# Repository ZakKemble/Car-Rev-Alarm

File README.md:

Car Rev Alarm and Gear Indicator
================================

A DIY Car rev alarm and gear indicator.

http://blog.zakkemble.co.uk/car-rev-alarm-and-gear-indicator/

---

Zak Kemble

contact@zakkemble.co.uk

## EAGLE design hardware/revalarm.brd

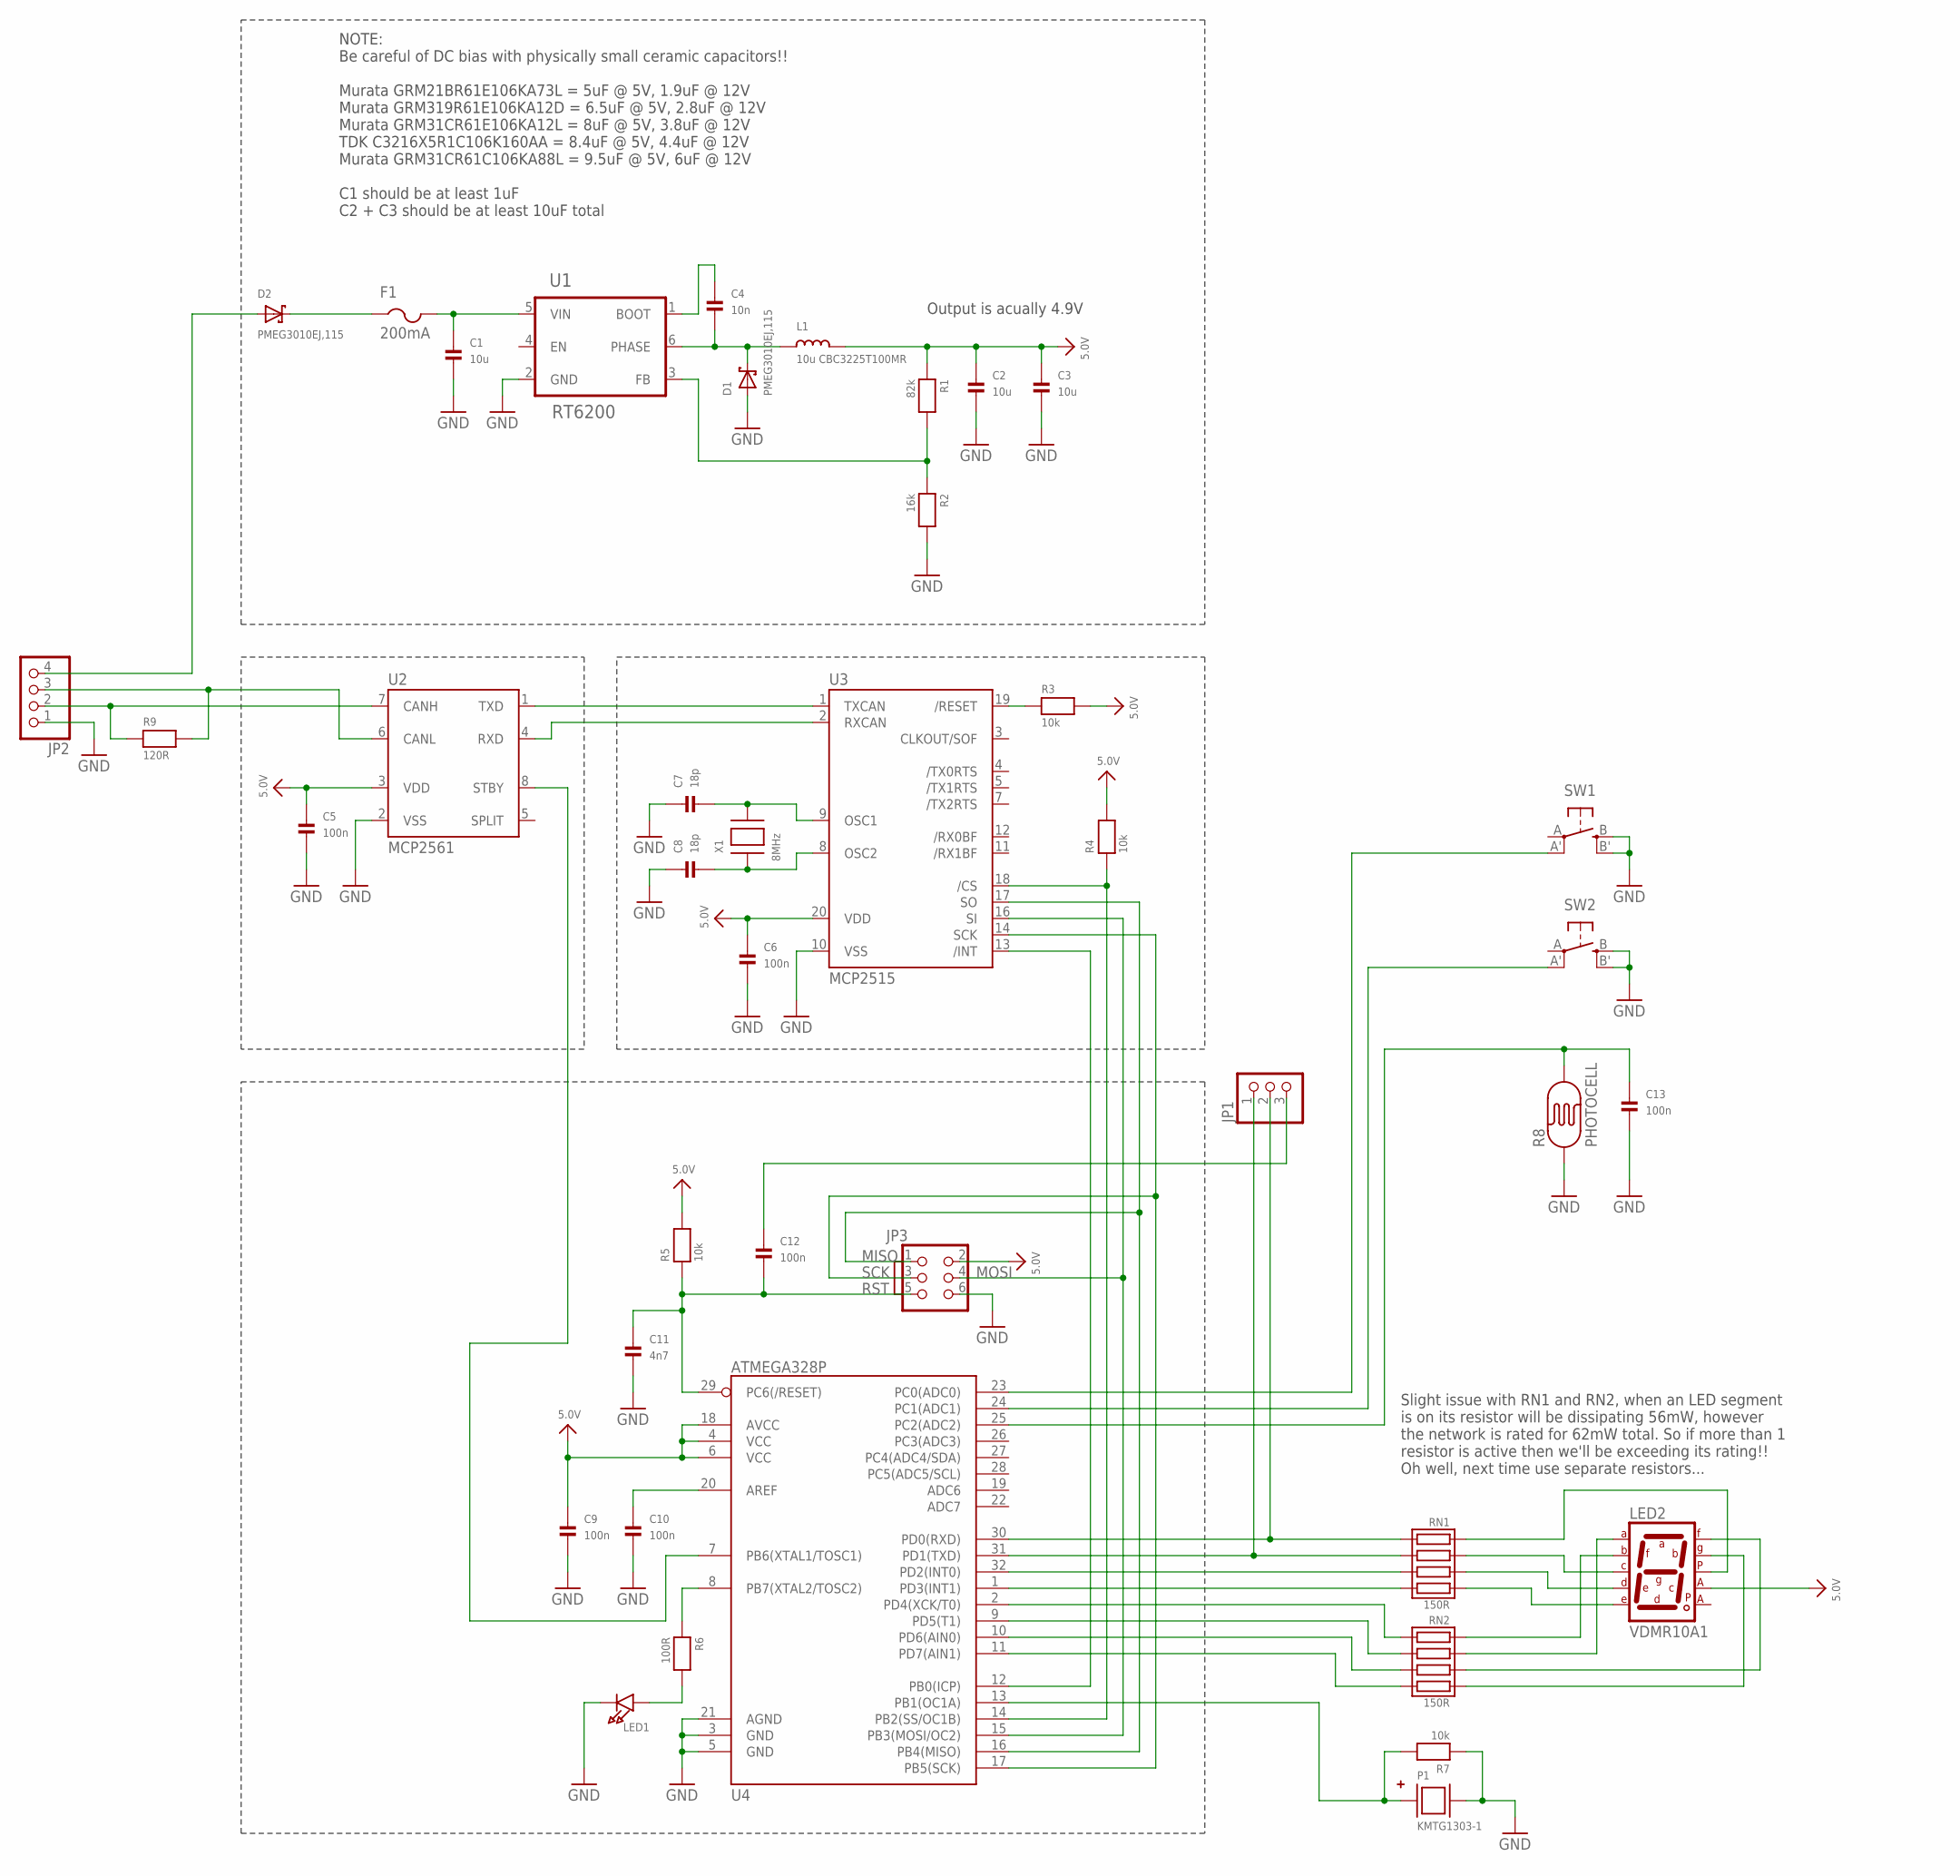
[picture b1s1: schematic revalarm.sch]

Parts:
C1, C2, C3: 10u; 1206
C4: 10n; 0402
C5, C6, C9, C10, C12, C13: 100n; 0402
C7, C8: 18p; 0402
C11: 4n7; 0402
D1, D2: PMEG3010EJ,115; SOD-323
F1: 200mA; 1206
JP1: PINHD-1X3; 1X03
JP2: PINHD-1X4; 1X04
JP3: ISP6PINPOGO_PIXELRGB; POGO60PIN_PIXELRGB
L1: 10u CBC3225T100MR; 1210K
LED1: LED0805_NOOUTLINE; CHIPLED_0805_NOOUTLINE
LED2: VDMR10A1; 7SEG-SMD
P1: KMTG1303-1; KMTG1303
R1: 82k; 0402
R2: 16k; 0402
R3, R4, R5, R7: 10k; 0402
R6: 100R; 0402
R8: PHOTOCELL
R9: 120R; 1206
RN1, RN2: 150R; RESPACK_4X0603
SW1, SW2: SPST_TACTMC32882; TACT_SMD4
U1: RT6200; SOT23-6_SM_PAD
U2: MCP2561; SOIC8_150MIL_SMPAD
U3: MCP2515; TSSOP20
U4: ATMEGA328P; TQFP32-08
X1: 8MHz; NX5032

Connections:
5.0V: C2.1, C3.1, C5.1, C6.1, C9.1, JP3.2, L1.2, LED2.COMM1 (CA1), R1.1, R3.2, R4.2, R5.2, U2.3 (VDD), U3.20 (VDD), U4.4 (VCC), U4.6 (VCC), U4.18 (AVCC)
GND: C1.2, C2.2, C3.2, C5.2, C6.2, C7.1, C8.1, C9.2, C10.2, C11.2, C13.2, D1.A, JP2.1, JP3.6, LED1.C, P1.P$2 (GND), R2.2, R7.1, R8.1, SW1.B (S), SW1.B' (S1), SW2.B (S), SW2.B' (S1), U1.2 (GND), U2.2 (VSS), U3.10 (VSS), U4.3 (GND), U4.5 (GND), U4.21 (AGND)
MISO: JP3.1, U3.17 (SO), U4.16 (PB4(MISO))
MOSI: JP3.4, U3.16 (SI), U4.15 (PB3(MOSI/OC2))
unnamed: C8.2, U3.8 (OSC2), X1.P$1
unnamed: C13.1, R8.2, U4.25 (PC2(ADC2))
unnamed: U2.4 (RXD), U3.2 (RXCAN)
unnamed: U2.1 (TXD), U3.1 (TXCAN)
unnamed: R4.1, U3.18 (/CS), U4.14 (PB2(SS/OC1B))
unnamed: C12.1, JP1.3
unnamed: RN2.6, U4.10 (PD6(AIN0))
unnamed: D2.C, F1.1
unnamed: C7.2, U3.9 (OSC1), X1.P$2
unnamed: LED2.G, RN2.4 (7)
unnamed: JP1.2, RN1.8 (2), U4.30 (PD0(RXD))
unnamed: C10.1, U4.20 (AREF)
unnamed: R3.1, U3.19 (/RESET)
unnamed: LED1.A, R6.2
unnamed: JP1.1, RN1.7 (4), U4.31 (PD1(TXD))
unnamed: RN1.6, U4.32 (PD2(INT0))
unnamed: RN1.5 (8), U4.1 (PD3(INT1))
unnamed: RN2.8 (2), U4.2 (PD4(XCK/T0))
unnamed: RN2.7 (4), U4.9 (PD5(T1))
unnamed: LED2.F, RN2.3 (5)
unnamed: RN2.5 (8), U4.11 (PD7(AIN1))
unnamed: LED2.A, RN2.2 (3)
unnamed: C1.1, F1.2, U1.5 (VIN)
unnamed: R1.2, R2.1, U1.3 (FB)
unnamed: C4.1, U1.1 (BOOT)
unnamed: C4.2, D1.C, L1.1, U1.6 (PHASE)
unnamed: D2.A, JP2.4
unnamed: JP2.2, R9.1, U2.7 (CANH)
unnamed: JP2.3, R9.2, U2.6 (CANL)
unnamed: U2.8 (STBY), U4.7 (PB6(XTAL1/TOSC1))
unnamed: P1.P$1 (VCC), R7.2, U4.13 (PB1(OC1A))
unnamed: LED2.B, RN2.1
unnamed: LED2.D, RN1.3 (5)
unnamed: LED2.E, RN1.4 (7)
unnamed: LED2.C, RN1.2 (3)
unnamed: LED2.DP, RN1.1
unnamed: U3.13 (/INT), U4.12 (PB0(ICP))
unnamed: SW1.A' (P1), U4.23 (PC0(ADC0))
unnamed: SW2.A' (P1), U4.24 (PC1(ADC1))
unnamed: R6.1, U4.8 (PB7(XTAL2/TOSC2))
RST: C11.1, C12.2, JP3.5, R5.1, U4.29 (PC6(/RESET))
SCK: JP3.3, U3.14 (SCK), U4.17 (PB5(SCK))

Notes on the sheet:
NOTE: Be careful of DC bias with physically small ceramic capacitors!! Murata GRM21BR61E106KA73L = 5uF @ 5V, 1.9uF @ 12V Murata GRM319R61E106KA12D = 6.5uF @ 5V, 2.8uF @ 12V Murata GRM31CR61E106KA12L = 8uF @ 5V, 3.8uF @ 12V TDK C3216X5R1C106K160AA = 8.4uF @ 5V, 4.4uF @ 12V Murata GRM31CR61C106KA88L 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
Output is acually 4.9V
Slight issue with RN1 and RN2, when an LED segment is on its resistor will be dissipating 56mW, however the network is rated for 62mW total. So if more than 1 resistor is active then we'll be exceeding its rating!! Oh well, next time use separate resistors...

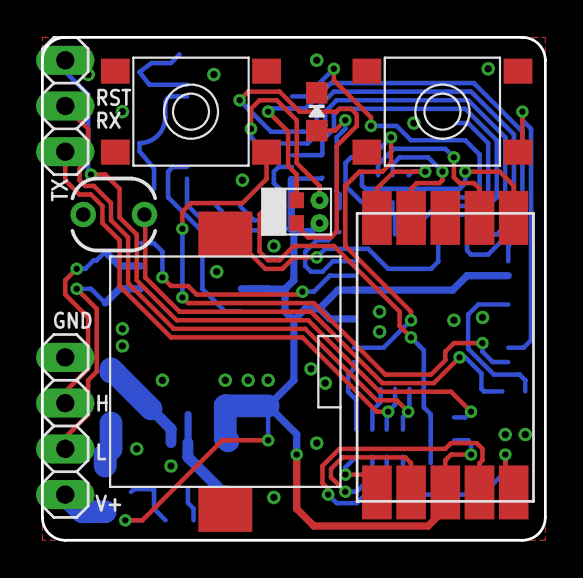
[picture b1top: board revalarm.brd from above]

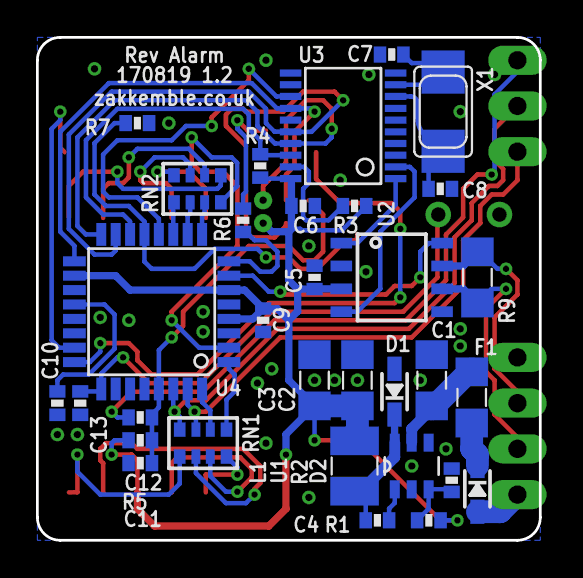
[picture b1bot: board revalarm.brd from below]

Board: 2 copper layers, 27.9 x 27.9 mm, 41 parts (32 on the bottom side), 46 nets.

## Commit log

2017-08-19 :lollipop: Added .gitattributes & .gitignore files
2017-08-19 Initial commit
    Initial commit
2017-08-19 Readme fix
2017-08-19 Add MCP_CAN_lib submodule

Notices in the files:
parts and their libraries:
microbuilder: This work is placed in the public domain, and may be freely used for commercial and non-commercial work with the following conditions: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
SparkFun-DigitalIC: Licensing: CC v3.0 Share-Alike You are welcome to use this library for commercial purposes.
